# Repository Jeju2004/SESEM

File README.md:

# SESEM: indoor BLE safety monitoring for a home for the aged

**An ESP32 wearable, three BLE zone beacons and a door sensor node that tell caregivers which room a resident is in and raise SOS and restricted-door alerts on a phone dashboard, with no internet connection required.**

*Electronics Design (ECEA120D), Section C1, Mapúa University, October 2026. Authors: Chester John B. Cirio and Pathrish Anne R. Cruz. Adviser: Engr. Glenn V. Magwili. The prototype is called SESEMSG in the final paper (TroDes in earlier drafts). It was defended before a three-member panel on 1 October 2026.*

## My part

Two-person team, adviser-approved design decisions.

- **Led system architecture and hardware selection.** Chose BLE over UWB, Wi-Fi RSSI, RFID and GPS with a weighted decision matrix (BLE 4.30, UWB 3.40, Wi-Fi RSSI 3.35, RFID 2.75, GPS 2.25; the scores are the team's assessment, paper section 3.12), and selected the ESP32 and the boost power chain.
- **Designed the wearable's single-sided PCB in KiCad** (69 × 66 mm; 0 design-rule errors, 0 unconnected pads) **and its 3D-printed PLA enclosure.**
- **Redesigned the wearable's power chain** to a boost topology when no low-dropout regulator could be sourced in time, then traced a power-path fault from measured voltages (battery 3.83 V, converter output 3.25 V against 5.0 V expected).

*Built with AI coding assistance: parts of the firmware, dashboard code and documentation were written with an AI assistant (Claude), so some commits in the history carry its name. The hardware design, decisions and testing are the authors'.*

## What it does

- **Zone tracking.** The wearable listens for iBeacon advertisements, smooths each signal, and reports the zone of the strongest beacon. It never estimates distance. Three zones were demonstrated: bedroom wing and dining hall (safe), medicine room (restricted).
- **SOS.** One, two or three button presses set the urgency; holding the button for 3 s cancels an open SOS. A caregiver acknowledges it on the dashboard and the wearable returns to normal.
- **Restricted door.** A reed switch on the medicine-room door raises an alert when it opens.
- **Heart rate and battery** are reported to the dashboard (heart rate is informational, not clinical).
- **No internet needed.** The door node doubles as a stand-alone hub: it runs its own Wi-Fi network and serves the caregiver dashboard to phones. The same firmware can instead report to a computer on a facility network.
- **Network loss.** The wearable queues events while the link is down and delivers them when it reconnects.

## System block diagram

*(a) Stand-alone hub as demonstrated. (b) Facility-network alternative with a computer running the dashboard. Remote viewing through a cloud relay is shown dashed: it was built and tested locally and not deployed.*

## Photos and renders

**Wearable, lid removed.** ESP32 DevKitC on the etched single-sided Rev C3 board, MAX30102 heart-rate sensor, SOS button, buzzer with transistor driver and status LED.

**Door node and beacon node, lids removed.** Both are an ESP32 DevKitC on a 5 × 7 cm perfboard in a printed enclosure. The door node adds a reed switch and magnet on a screw terminal (GPIO 18).

**Caregiver dashboard on a phone.** Home (zone, heart rate, door), SOS banner with Acknowledge, open alerts, and an activity history that records who acknowledged. Names and readings shown are test data.

**Wearable enclosure, exploded view.** A 3-D model render, not a photograph. The enclosure is printed in PLA with a captive SOS plunger and a fingertip window over the heart-rate sensor.

**Wearable board, Revision C3.** KiCad 3-D view of the single-sided carrier board (69 × 66 mm) for the ESP32 and sensor modules. This is a render, not a photograph.

## Measured results

All values come from the final paper and the raw captures it cites. These are small prototype tests, not field trials.

| Test | Result | Notes |
|---|---|---|
| Zone classification, Test 2 Run 1 (24 Sep 2026, earlier firmware) | 56.2 % overall (278 of 495 samples); 23.2 % unresolved; no errors across the tested wall | One run, 16 labelled points. Two of the three beacons shared one open room, which caused the lower score. |
| Coverage | Beacon received at every tested distance up to 6 m in line of sight, at least 11.9 dB above the −88 dBm detection floor | Range beyond 6 m and other wall types were not measured. |
| Signal strength vs distance (Test 1) | Fitted path-loss exponents 0.28 and 0.55 (free space is 2.0) | This is why zones are chosen by comparing beacons, not by estimating distance. |
| SOS delivery to the hub | Median 295 ms, maximum 408 ms (n = 6) | Timed on the wearable's own clock up to the hub's reply; the full event-to-phone delay was not timed. |
| Restricted-door detection | 4 of 4 openings detected | 3 on 29 Sep and 1 in the 30 Sep demonstration. The planned 20 cycles were not run. |
| Dashboard checks | Backend self-test 38 of 38; hub network checks 17 of 17 | |
| Multi-resident load test | 10 to 200 simulated wearables on one laptop; every resident name, zone and SOS attributed correctly | Simulated. The two-wearable hardware test was not performed. |

*Test 1, received signal strength against distance (run A), with the −88 dBm detection floor and the 11.9 dB margin at 6 m.*

### Limitations: not measured

- **Battery runtime.** Not measured. The calculated runtime for the 2000 mAh cell is about 20 h in the test profile and about 33 h in the low-power profile, against a 24 h target.
- **Zone accuracy on the final firmware.** Not reported; the capture of that run was overwritten.
- **Complete event-to-phone delay.** Not timed; the paper gives a stage-by-stage estimate only.
- **Coverage beyond 6 m and through other wall types.** Not measured.
- **Two-wearable hardware test.** Not performed.

## Tech stack

| Layer | What was used |
|---|---|
| Microcontroller | ESP32 (ESP32-WROOM-32 DevKitC) in all three device types: wearable, beacon, door node |
| Wireless | Bluetooth Low Energy iBeacon advertising (beacons at +9 dBm, every 100 ms), passive scanning on the wearable; Wi-Fi (WPA2) from wearable to hub |
| Firmware | PlatformIO with the Arduino framework |
| Dashboard and backend | Python, FastAPI and SQLite, as a web page that opens on any phone browser; the door node serves the same API as a stand-alone hub |
| Sensors and power | MAX30102 heart-rate sensor, reed switch, Li-Po cell with TP4056 charger and MT3608 boost converter, resistor divider for battery sensing |
| Hardware design | KiCad 9 (schematic, board, design-rule check), perfboard for beacons and door node |
| Enclosures | Blender models, printed in PLA on a Bambu Lab A1 |
| Tools | Python analysis scripts for the test data, Git |

## Repository layout

```
firmware/
  beacon_node/      ESP32 iBeacon advertiser, one flashed board per zone
  wearable/         ESP32 wearable: BLE scan, zone logic, SOS, heart rate, battery, Wi-Fi
  door_sensor/      ESP32 reed switch node for restricted doors
tools/
  rssi_calibration/ serial capture and Test 1/2/3 analysis scripts
dashboard/          caregiver web dashboard: FastAPI + SQLite, simulator, self-tests
docs/               programming guide, test guides, zone config, project status
CHANGELOG.md        dated log of every code change
```

**Quick start**

- Firmware: see [docs/BOARD_PROGRAMMING_GUIDE.md](docs/BOARD_PROGRAMMING_GUIDE.md).
- Tests: see [docs/PHASE1_TEST_GUIDE.md](docs/PHASE1_TEST_GUIDE.md).
- Dashboard data contract (what the firmware posts): [docs/DASHBOARD_BUILD_BRIEF.md](docs/DASHBOARD_BUILD_BRIEF.md).
- Team notes and the full project map: [docs/PROJECT_MAP.md](docs/PROJECT_MAP.md).

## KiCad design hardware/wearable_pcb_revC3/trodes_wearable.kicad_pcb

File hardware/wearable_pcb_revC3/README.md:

# TroDes Wearable Carrier Board — KiCad project (Rev C3)

26 September 2026. KiCad 9 format. Open **`trodes_wearable.kicad_pro`**.
Earlier revisions are kept beside it as `.bak` files: Rev C2 (26 Sep), Rev C1
(26 Sep) and Rev C (23 Sep).

Plan: **only the wearable is etched**; the beacons and the door node stay on
perfboard.

## What changed from Rev C2

| Rev C2 | Rev C3 |
|---|---|
| TP4056 and MT3608 as plain 1×4 rows in the wrong order (B+ B− OUT+ OUT−; IN+ IN− OUT+ OUT−) | Wire pads that mirror each module's own terminals and are labelled like the module |
| The battery came onto the board (BT1) and went straight back out to the TP4056 | The battery solders **directly to the TP4056 B+/B−**. BT1 is off the board |
| — | The team moved the whole board onto the A4 drawing sheet (+112 mm, +53.5 mm). The design itself is unchanged |
| "TRODES C2 COPPER SIDE" text etched in copper | **Removed** at the team's request (27 Sep). The ground pour fills its place |

## Off-board power wiring (power deck under the PCB)

```
Battery + ──► TP4056 B+          TP4056 OUT+ ──► J1 OUT+ (square pad)
Battery − ──► TP4056 B−          TP4056 OUT− ──► J1 OUT−
   (JST-PH pigtail on the TP4056 so the battery unplugs)

Toggle switch:  middle lug (common) ──► SW1 pad 2 (VBAT)
                outer lug           ──► SW1 pad 1 (VSW)      pad 3 unused

MT3608:  VIN+ ◄── J2 VIN+ (square pad)     VIN−  ◄── J2 VIN−
         VOUT+ ──► J2 VOUT+                VOUT− ──► J2 VOUT−
```

- **J2** is laid out like the MT3608 turned a quarter turn: top row VIN+ VIN−,
  bottom row VOUT+ VOUT−.
- **Set the MT3608 to 5.0 V on the bench before wiring VOUT to J2.**
- **Fuel gauge (U3) battery lead:** plug a JST-PH lead into its JST and connect
  the **red** wire to TP4056 OUT+ (or to J1 OUT+). Leave the black wire
  unconnected.

## Verified in KiCad 9.0.3

| Check | Result |
|---|---|
| PCB design-rule check, zones refilled | **0 errors, 0 warnings, 0 unconnected pads** |
| Schematic ↔ PCB parity | **0 differences** |
| Schematic ERC | **0 errors, 0 warnings** |

Reports: `DRC_report_RevC3.txt`, `ERC_report_RevC3.txt`.

**Six courtyard overlaps are excluded on purpose**, each checked against the
real part sizes:

| Overlap | Why it is fine |
|---|---|
| U1 with Q1 | The devkit is raised on its headers; the Q1 body lies outside the devkit outline |
| U2 with R5 and with R6 | The flat resistors lie under the raised module |
| C1 with C2 | 0.6 mm clear |
| BZ1 with Q1 | 1.6 mm clear |
| R3 with C4 | Clear |

"Footprint differs from library" notices are switched off because the enlarged
etching pads are deliberate. "Silkscreen over copper" notices are switched off
too: this home-etched board has no printed silkscreen.

### Design rules and measured margins (27 Sep, for UV etching on FR-2)

**Rules:**
- **Netclass:** 0.4 mm clearance, 0.6 mm default track.
- **`trodes_wearable.kicad_dru`:**
  - tracks and pads ≥ 1 mm from the edge;
  - pad ring ≥ 0.45 mm;
  - track ≥ 0.5 mm.

The netclass had been silently reset to KiCad's 0.2 mm default by a scripted
save. It was restored on 27 Sep, and the real copper was measured.

| Worst case on the copper | Value |
|---|---|
| Gap between different nets | 0.47 mm (R1 pad 2 ↔ Q1 emitter) |
| Gap to the ground pour | 0.45 mm |
| Narrowest track | 0.6 mm |
| Tracks and pads to the board edge | 1.1 mm (ground pour 0.5 mm) |
| Pad ring | 0.6 mm (0.8 and 1.3 mm holes), 0.45 mm (1.0 mm header holes) |
| Hole to hole | 1.5 mm |

**FR-2 changes (27 Sep):**
- **Pads enlarged:**
  - resistors, C1, C2, C4, D1, Q1: 2.0 mm;
  - MAX30102, MAX17043, SW1: 1.9 mm;
  - LED: 2.0 mm;
  - SOS switch: 3.2 × 2.5 mm.
- Fuel-gauge tracks widened to 0.6 mm.
- J1 moved 1.27 mm up; it was 0.85 mm from the edge.
- The left +3V3 track moved 0.5 mm in from the edge.
- One VBAT track corner moved away from SW1's spare pad.

## Every connection on the board

| Net | ESP32 pin (team pinout) | Goes to |
|---|---|---|
| +3V3 | 1 (3V3) | C3 +, R5, R6, U2 VIN, U3 VCC |
| +5V | 19 (V5) | **J2 VOUT+**, BZ1 +, D1 K, C1 +, C2 |
| VBAT | — | **J1 OUT+**, SW1 pad 2 (common), R3 |
| VSW | — | SW1 pad 1 → **J2 VIN+** |
| SDA / SCL (heart rate) | 22 (IO22) / 25 (IO21) | U2, R5 / R6 pull-ups |
| FG_SDA / FG_SCL (fuel gauge) | 32 (IO4) / 31 (IO16) | U3 (module pull-ups) |
| SOS_BTN | 11 (IO27) | SW2 SOS legs (other legs to GND) |
| BUZZ_DRV | 9 (IO25) | R1 1 k → Q1 base |
| LED_STAT | 34 (IO2) | R2 330 Ω → D2 |
| VBAT_SENSE | 5 (IO34) | R3/R4 100 k divider, C4 |
| BZ1 − | — | Q1 collector, D1 anode |
| GND | 14, 20, 26 | The pour: **J1 OUT−, J2 VIN−, J2 VOUT−**, C1–C4, D2 K, Q1 E, R4, SW2, U2, U3 |

## Parts as built

| Ref | Part | Mounting |
|---|---|---|
| U1 | ESP32 DevKitC 38-pin, 55 × 28 mm | 2 × 1×19 female headers (5 mm), USB to the right |
| U2 | MAX30102 module 20 × 15 mm, 2 × 4 | Female headers, **sensor side up**. Set its pull-up jumper to 3V3 |
| U3 | MAX17043 fuel gauge (SparkFun layout), 2 × 3 | Female headers, parts side up, JST to the right |
| SW2 | 12 × 12 mm tact switch | Soldered |
| BZ1 | 12 mm passive buzzer, legs 7.6 mm apart | + leg on the square pad |
| Q1 | 2N2222A, E-B-C | Flat face toward you |
| J1 | TP4056 + DW01 (USB Type-C, 28 × 17 mm) | Off-board, 2 wires |
| J2 | MT3608 (36 × 18 × 6 mm) | Off-board, 4 wires |
| SW1 | SPDT mini toggle, 3 A | Panel-mounted, 2 wires |

**Still to confirm:**
- the fuel gauge's back labels (ALT GND VCC / QST SCL SDA) when it arrives;
- the ESP32 pin-1-to-antenna-edge distance (assumed 7.0 mm).

## Firmware

The fuel gauge uses `Wire1` on IO4 (SDA) and IO16 (SCL); the heart-rate bus
is on IO22/IO21. Committed as `8f14d4f`.

## Etching sheets (`artwork/`)

| File | Use |
|---|---|
| **`UV_MASK_NEGATIVE_trodes_wearable-B_Cu.pdf`** | UV mask for **dry film** or other negative resist: copper is clear, gaps are black |
| **`UV_MASK_POSITIVE_trodes_wearable-B_Cu.pdf`** | UV mask for **pre-sensitised positive** boards or positive spray resist: copper is black |
| `TroDes_Wearable_RevC3_ComponentPlacement.pdf` | Where the parts go and which wire goes where |
| `TroDes_Wearable_RevC3_Schematic.pdf` | Schematic |
| `TroDes_Wearable_RevC3_3D_top.png` | 3D preview |

**KiCad plot settings** (File → Plot, saved in the board):

| Setting | Value |
|---|---|
| Format | PDF, black and white |
| Include layers | **B.Cu** |
| Plot on all layers | **Edge.Cuts** |
| Drill marks | Small |
| Scale | 1:1 |
| Mirrored | Off |
| Negative | Off for the positive mask, **On** for the negative mask |
| Drawing sheet | Off |
| Output | `artwork/` (KiCad names the file `trodes_wearable-B_Cu.pdf`; renamed afterwards) |

- **Print** on transparency film at **100% / Actual size**, A4 landscape, with
  no fit-to-page. The outline must measure **69.0 × 66.0 mm**.
- **Expose with the printed side DOWN** on the resist. Looking through the
  film, the antenna slot is then on the **RIGHT**. The mask is not mirrored on
  purpose.
- **Full procedure:** `Wearable PCB UV Etching Plan.md`, covering resist,
  exposure test strip, developing, etching, drilling, cutting, and soldering
  on FR-2.
- **Do not use the older toner-transfer sheets** (Rev C2 or earlier).

## Related

[[Work Log]] · [[Enclosure Measurement Sheet]] · [[ESP32 DevKitC Pinout]]

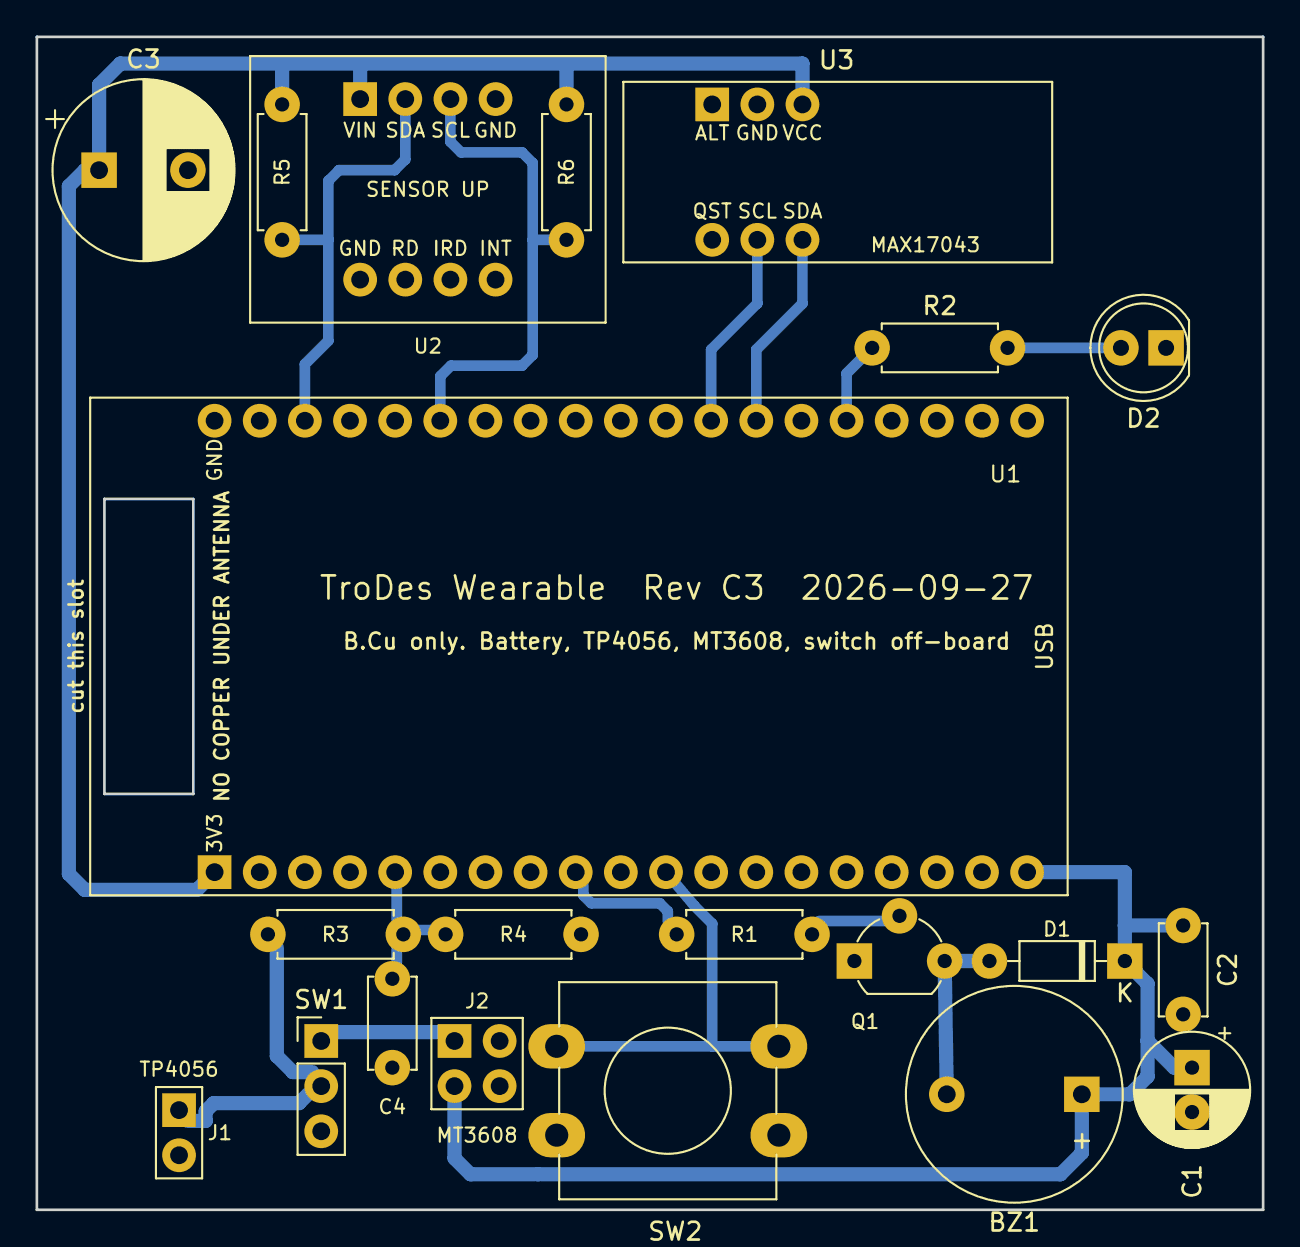
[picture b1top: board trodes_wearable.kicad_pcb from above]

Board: 2 copper layers, 69.0 x 66.0 mm, 21 parts (0 on the bottom side), 16 nets.

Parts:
BZ1: Piezo; Buzzer_12x9.5RM7.6
C1: 100uF; CP_Radial_D6.3mm_P2.50mm
C2, C4: 100nF; C_Disc_D5.0mm_W2.5mm_P5.00mm
C3: 470uF; CP_Radial_D10.0mm_P5.00mm
D1: 1N4148; D_DO-35_SOD27_P7.62mm_Horizontal
D2: LED; LED_D5.0mm
J1: TP4056 OUT; TP4056_OUT_WirePads
J2: MT3608 IN/OUT; MT3608_WirePads_2x2
Q1: 2N2222; TO-92_Wide
R1: 1k; R_Axial_DIN0207_L6.3mm_D2.5mm_P7.62mm_Horizontal
R2: 330R; R_Axial_DIN0207_L6.3mm_D2.5mm_P7.62mm_Horizontal
R3, R4: 100k; R_Axial_DIN0207_L6.3mm_D2.5mm_P7.62mm_Horizontal
R5, R6: 4.7k; R_Axial_DIN0207_L6.3mm_D2.5mm_P7.62mm_Horizontal
SW1: Battery / Off; PinHeader_1x03_P2.54mm_Vertical
SW2: SOS; SW_PUSH-12mm
U1: ESP32-DevKitC-38; ESP32-DevKitC-38_55x28mm_Socket
U2: MAX30102; MAX30102_Module_2x4_Socket
U3: MAX17043; MAX17043_Module_2x3_Socket

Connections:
+3V3: C3.1, R5.1, R6.1, U1.1, U2.1, U3.3
+5V: BZ1.1, C1.1, C2.1, D1.1, J2.3, U1.19
/BUZZ_DRV: R1.1, U1.9
/FG_SCL: U1.31, U3.5
/FG_SDA: U1.32, U3.6
/LED_STAT: R2.1, U1.34
/SCL: R6.2, U1.25, U2.3
/SDA: R5.2, U1.22, U2.2
/SOS_BTN: SW2.2, U1.11
/VBAT_SENSE: C4.1, R3.2, R4.1, U1.5
/VSW: J2.1, SW1.1
GND: C1.2, C2.2, C3.2, C4.2, D2.1, J1.2, J2.2, J2.4, Q1.1, R4.2, SW2.1, U1.14, U1.20, U1.26, U2.4, U3.2
unnamed: BZ1.2, D1.2, Q1.3
unnamed: D2.2, R2.2
unnamed: Q1.2, R1.2
VBAT: J1.1, R3.1, SW1.2
